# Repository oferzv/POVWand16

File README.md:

# POVWand16

POVWand16 is a 16 LED persistence-of-vision wand. When the wand is moved
through the air, the firmware flashes a vertical column of LEDs fast enough
that the viewer sees complete text or simple bitmap graphics suspended in the
motion path.

The repository contains both sides of the project:

- Arduino firmware for driving the LED column and selecting messages or
  graphics.
- Autodesk Eagle schematic and board layout files for the custom PCB.
- Manufacturing outputs, including a BOM spreadsheet and Gerber archive.

## Project Overview

The design is based around an Arduino Nano-compatible controller connected to
16 individual LEDs. Each LED has its own 100 ohm series resistor. The firmware
writes directly to the AVR port registers for speed, allowing all 16 LEDs to be
updated as a two-byte column pattern.

A trigger input on Arduino analog pin A4 is used to step through the available
display content. The current firmware alternates between text messages and
graphics. Text can be rendered with either the English font table or the Hebrew
font table stored in program memory.

The hardware is intended to be a self-contained handheld wand. The PCB includes
the Arduino Nano footprint, the LED column, a 9 V battery holder, a power slide
switch, a tactile switch, and several header connectors.

## Repository Layout

```text
.
+-- Firmware
|   +-- README.md
|   +-- POVWand16_SW_heb
|       +-- POVWand16.ino
|       +-- font.h
|       +-- python
|           +-- pandaTestFormat.py
+-- Hardware
|   +-- V1_1
|       +-- Eagle
|       |   +-- POVWand16.brd
|       |   +-- POVWand16.sch
|       +-- Manufacturing
|           +-- BOM
|           |   +-- POVWand16_BOM.xlsx
|           +-- Gerber
|               +-- POVWand16_2020-03-09.zip
+-- README.md
```

## Hardware

The hardware design files live under `Hardware/V1_1`.

Main board elements:

- Arduino Nano 3.0-compatible module footprint.
- 16 through-hole 3 mm LEDs labeled `D1` through `D16`.
- 16 through-hole 100 ohm LED current-limiting resistors labeled `R1` through
  `R16`.
- 9 V battery holder footprint.
- Slide power switch.
- 6 mm momentary tactile switch.
- Additional 1x08 and 1x18 headers for board connections and expansion.

The Eagle files are:

- `Hardware/V1_1/Eagle/POVWand16.sch` - schematic.
- `Hardware/V1_1/Eagle/POVWand16.brd` - PCB layout.

Manufacturing files are:

- `Hardware/V1_1/Manufacturing/BOM/POVWand16_BOM.xlsx` - bill of materials.
- `Hardware/V1_1/Manufacturing/Gerber/POVWand16_2020-03-09.zip` - Gerber
  output for PCB fabrication.

## Firmware

The firmware is an Arduino sketch located at:

```text
Firmware/POVWand16_SW_heb/POVWand16.ino
```

Supporting files:

- `font.h` contains the English and Hebrew font tables in `PROGMEM`.
- `python/pandaTestFormat.py` is a small helper script for converting Hebrew
  text into the character order/encoding expected by the sketch.

The sketch uses Arduino pins 2 through 17 as the 16 LED outputs:

```cpp
const byte LEDpins[] = {2, 3, 4, 5, 6, 7, 8, 9, 10, 11, 12, 13, 14, 15, 16, 17};
```

The trigger input is on pin 18, which corresponds to Arduino A4:

```cpp
const byte triggerPin = 18;
```

Display timing is controlled by three constants:

- `charDelay` - spacing between characters.
- `tColDelay` - spacing between text columns.
- `gColDelay` - spacing between graphic columns.

The current firmware defines six text messages and two graphics. A trigger
press advances through the text messages, then advances through the graphics,
then returns to the first text message.

## Display Content

Text messages are defined in `POVWand16.ino` as `PROGMEM` strings:

```cpp
const char textString01 [] PROGMEM = "ARDIUNO - fqjafdya";
const char textString02 [] PROGMEM = "eqfyfxe jyha eay{q";
const char textString03 [] PROGMEM = "BRAVO!";
const char textString04 [] PROGMEM = "Hello";
const char textString05 [] PROGMEM = "WOW!";
const char textString06 [] PROGMEM = "Amazing";
```

Each message is paired with a font type in the `messages_new` table:

- `HEBFONT` selects the Hebrew font table.
- `ENGFONT` selects the English font table.

Graphics are stored as byte arrays in the `graphic` table. Each displayed
column is represented by two bytes, covering the full 16 LED height.

## Building and Uploading

Open `Firmware/POVWand16_SW_heb/POVWand16.ino` in the Arduino IDE or another
Arduino-compatible build environment.

Recommended target:

- Board: Arduino Nano or compatible.
- Processor: the option matching the installed Nano bootloader.
- Upload method: standard USB serial upload through the Nano.

After upload, power the wand and move it through the air. Use the trigger input
to cycle through the stored text and graphic displays.

## Customization Notes

To change displayed text:

1. Edit the `textStringXX` constants in `POVWand16.ino`.
2. Set each message's font type in `messages_new`.
3. Update `NUMBER_OF_ELEMENTS` if the number of messages changes.

To change graphics:

1. Edit the byte arrays in the `graphic` table.
2. Keep each graphic encoded as pairs of bytes per column.
3. Adjust the timing constants if the image appears stretched or compressed
   while waving the wand.

To change LED wiring:

1. Update `LEDpins` if using the slower `digitalWrite` helper path.
2. Update `setPorts()` if changing the direct AVR port mapping used by the
   main display loop.

## Attribution

The firmware is based on the JolliPOV Stick Arduino code from the Instructables
project
[Arduino Based POV Display Stick - JolliPOV Stick](https://www.instructables.com/Arduino-Based-POV-Display-Stick-JolliPOV-Stick/)
by [jollifactory](https://www.instructables.com/member/jollifactory/).

Credit and thanks to the original author for publishing the JolliPOV Stick
project instructions and example firmware.

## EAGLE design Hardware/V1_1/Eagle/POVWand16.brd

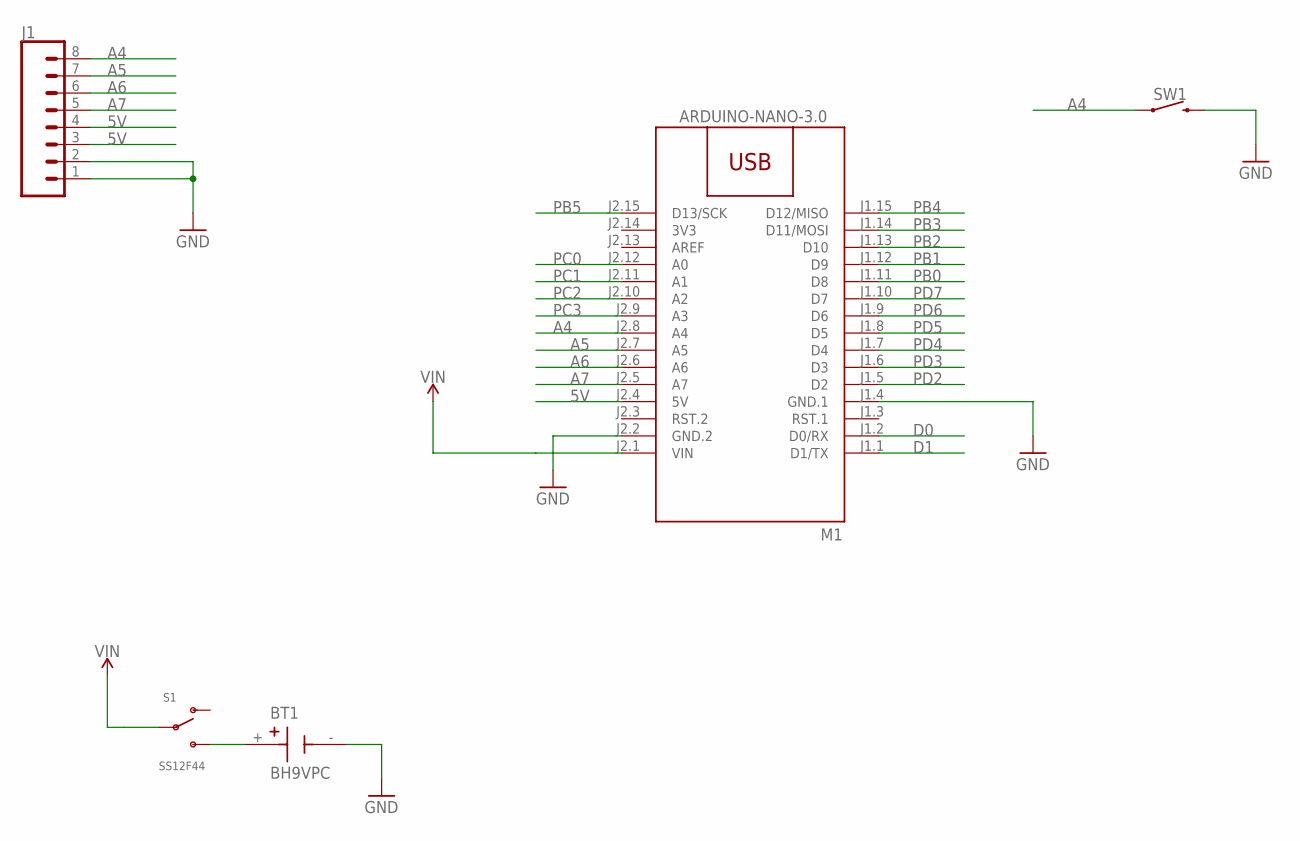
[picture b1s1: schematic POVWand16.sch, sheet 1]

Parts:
BT1: BH9VPC; BAT_BH9VPC
J1: CONN_08"; 1X08
M1: ARDUINO-NANO-3.0
S1: SS12F44; SS12F44G5
SW1: MOMENTARY-SWITCH-SPST_6X6MM; TACT_SW_PTH_6.0MM

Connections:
3V3: M1.J2.14 (3V3)
5V: J1.3, J1.4, M1.J2.4 (5V)
A4: J1.8, M1.J2.8 (A4), SW1.1, SW1.2 (1)
A5: J1.7, M1.J2.7 (A5)
A6: J1.6, M1.J2.6 (A6)
A7: J1.5, M1.J2.5 (A7)
D0: M1.J1.2 (D0/RX); also elsewhere on the board
D1: M1.J1.1 (D1/TX); also elsewhere on the board
GND: BT1.-, J1.1, J1.2, M1.J1.4 (GND.1), M1.J2.2 (GND.2), SW1.3 (2), SW1.4 (2); also elsewhere on the board
unnamed: BT1.+, S1.3 (S)
PB0: M1.J1.11 (D8); also elsewhere on the board
PB1: M1.J1.12 (D9); also elsewhere on the board
PB2: M1.J1.13 (D10); also elsewhere on the board
PB3: M1.J1.14 (D11/MOSI); also elsewhere on the board
PB4: M1.J1.15 (D12/MISO); also elsewhere on the board
PB5: M1.J2.15 (D13/SCK); also elsewhere on the board
PC0: M1.J2.12 (A0); also elsewhere on the board
PC1: M1.J2.11 (A1); also elsewhere on the board
PC2: M1.J2.10 (A2); also elsewhere on the board
PC3: M1.J2.9 (A3); also elsewhere on the board
PD2: M1.J1.5 (D2); also elsewhere on the board
PD3: M1.J1.6 (D3); also elsewhere on the board
PD4: M1.J1.7 (D4); also elsewhere on the board
PD5: M1.J1.8 (D5); also elsewhere on the board
PD6: M1.J1.9 (D6); also elsewhere on the board
PD7: M1.J1.10 (D7); also elsewhere on the board
VIN: M1.J2.1 (VIN), S1.2

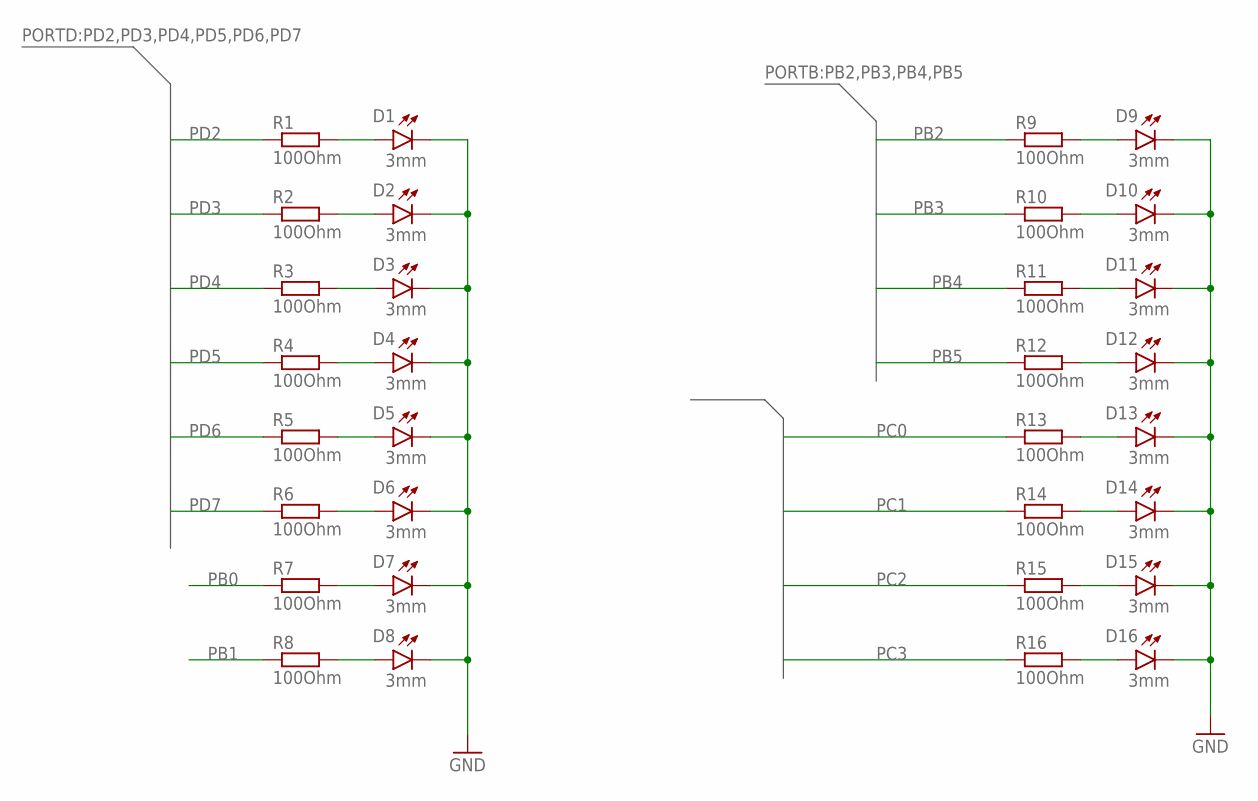
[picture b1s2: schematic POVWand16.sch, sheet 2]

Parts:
D1, D2, D3, D4, D5, D6, D7, D8, D9, D10, D11, D12, D13, D14, D15, D16: 3mm; LED3MM
R1, R2, R3, R4, R5, R6, R7, R8, R9, R10, R11, R12, R13, R14, R15, R16: 100Ohm; 0207/7

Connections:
GND: D1.K (C), D2.K (C), D3.K (C), D4.K (C), D5.K (C), D6.K (C), D7.K (C), D8.K (C), D9.K (C), D10.K (C), D11.K (C), D12.K (C), D13.K (C), D14.K (C), D15.K (C), D16.K (C); also elsewhere on the board
unnamed: D1.A, R1.2
unnamed: D2.A, R2.2
unnamed: D3.A, R3.2
unnamed: D4.A, R4.2
unnamed: D5.A, R5.2
unnamed: D6.A, R6.2
unnamed: D7.A, R7.2
unnamed: D8.A, R8.2
unnamed: D9.A, R9.2
unnamed: D10.A, R10.2
unnamed: D11.A, R11.2
unnamed: D12.A, R12.2
unnamed: D13.A, R13.2
unnamed: D14.A, R14.2
unnamed: D15.A, R15.2
unnamed: D16.A, R16.2
PB0: R7.1; also elsewhere on the board
PB1: R8.1; also elsewhere on the board
PB2: R9.1; also elsewhere on the board
PB3: R10.1; also elsewhere on the board
PB4: R11.1; also elsewhere on the board
PB5: R12.1; also elsewhere on the board
PC0: R13.1; also elsewhere on the board
PC1: R14.1; also elsewhere on the board
PC2: R15.1; also elsewhere on the board
PC3: R16.1; also elsewhere on the board
PD2: R1.1; also elsewhere on the board
PD3: R2.1; also elsewhere on the board
PD4: R3.1; also elsewhere on the board
PD5: R4.1; also elsewhere on the board
PD6: R5.1; also elsewhere on the board
PD7: R6.1; also elsewhere on the board

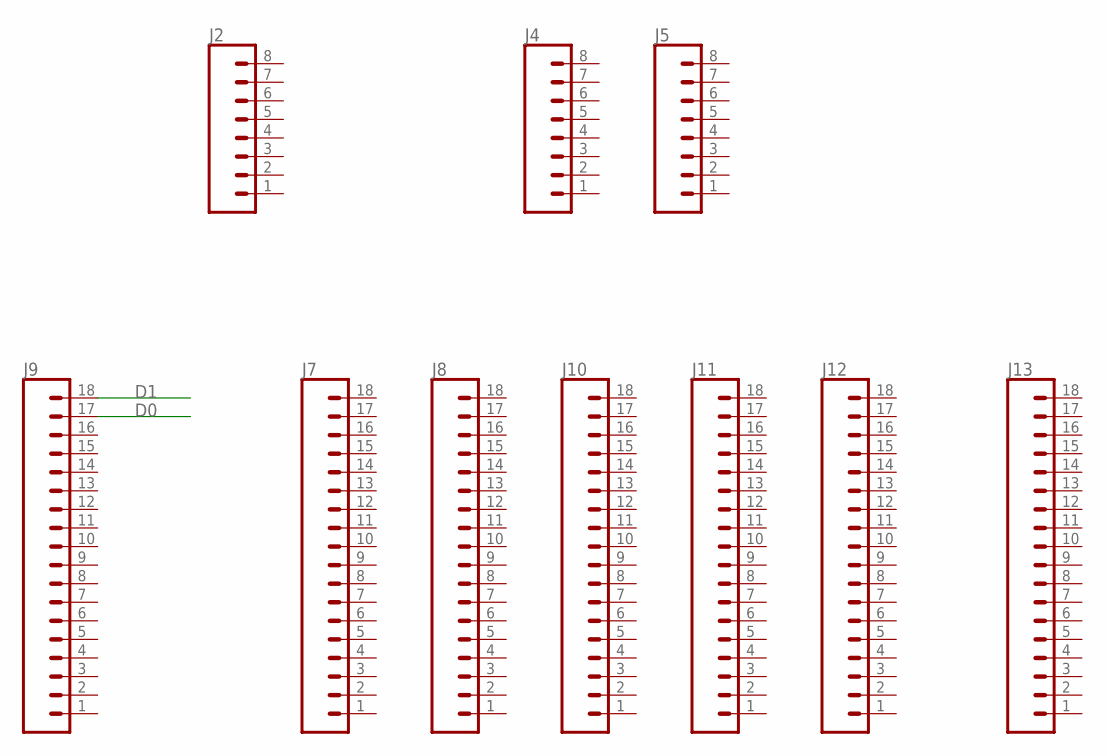
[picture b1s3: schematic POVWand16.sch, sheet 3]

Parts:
J2, J4, J5: CONN_08"; 1X08
J7, J8, J9, J10, J11, J12, J13: CONN_18; 1X18

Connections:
D0: J9.17; also elsewhere on the board
D1: J9.18; also elsewhere on the board

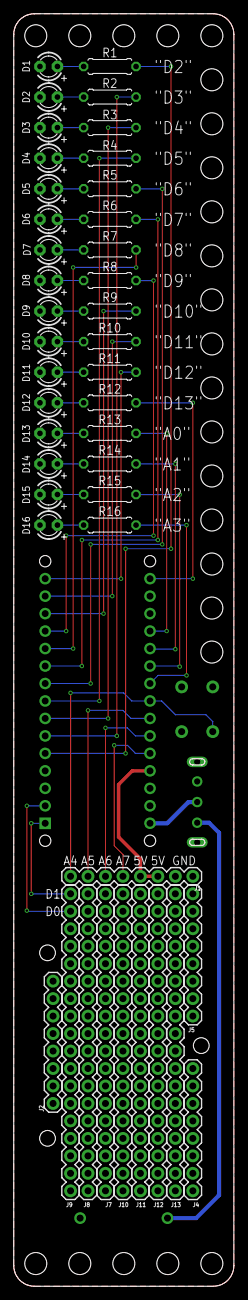
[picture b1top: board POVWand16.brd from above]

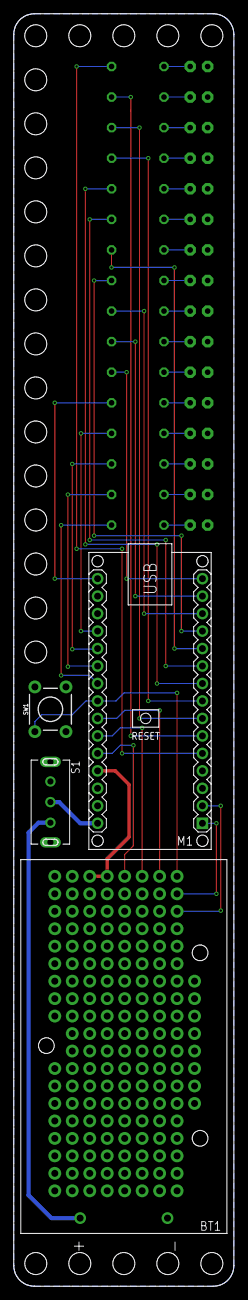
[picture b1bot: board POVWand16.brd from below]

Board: 2 copper layers, 32.0 x 185.0 mm, 47 parts (4 on the bottom side), 42 nets.

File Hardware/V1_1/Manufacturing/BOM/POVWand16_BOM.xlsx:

povTest BOM
# | Qty | Parts | MF | MPN | PRICE | TOTAL | VALUE | FOOTPRINT | DESCRIPTION
1 | 1 | SW1 | C&K | PTS645SM43-2 LFS | 0.04 | 0.04 |  | 6.00mm x 6.00mm | SWITCH TACTILE SPST-NO 0.05A 12V | https://www.taydaelectronics.com/electromechanical/switches-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
2 | 16 | R1, R2, R3, R4, R5, R6, R7, R8, R9, R10, R11, R12, R13, R14, R15, R16 |  |  | 1.2E-2 | 0.192 | 100Ohm | T/H |  | https://www.taydaelectronics.com/resistors/1-4w-metal-film-r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
3 | 16 | D1, D2, D3, D4, D5, D6, D7, D8, D9, D10, D11, D12, D13, D14, D15, D16 |  |  | 0.02 | 0.32 | 3mm | RADIAL 3MM |  | https://www.taydaelectronics.com/leds/round-leds/3mm-leds/le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
4 | 2 |  |  |  | 0.12 | 0.24 |  |  | 15 PIN 2.54MM SINGLE ROW FEMALE PIN HEADER | https://www.taydaelectronics.com/connectors-sockets/pin-head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
5 | 1 | M1 |  |  | 3.69 | 3.69 |  |  | NANO 3.0 CONTROLLER COMPATIBLE WITH ARDUINO NANO CH340 USB DRIVER | https://www.taydaelectronics.com/nano-3-0-controller-compati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
6 | 1 | BT1 | MPD _Memory | BH9VPC | 0.47 | 0.47 |  |  | Battery Holder _Open_ 9V 1 Cell PC Pin | https://www.taydaelectronics.com/9v-battery-holder-6.html
7 | 1 | S1 |  | SS12F44G5 | 0.05 | 0.05 |  |  | SLIDE SWITCH 1P2T THROUGH HOLE 0.5A 50VDC | https://www.taydaelectronics.com/electromechanical/switches-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
 |  |  |  |  |  | 5.0019999999999998

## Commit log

2026-06-06 Ignore Excel temporary files
2026-06-06 Add Hebrew string processing script and update README
    - Introduced a new Python script `pandaTestFormat.py` for processing Hebrew strings.
    - The script accepts a Hebrew string as input, decodes it, and outputs a modified version.
    - Added a README file to provide context and credit for the firmware based on the JolliPOV Stick project.
    - Included a new BOM Excel file for manufacturing reference.
2026-06-07 Update project README

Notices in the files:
parts and their libraries:
SparkFun-Connectors: Licensing: Creative Commons ShareAlike 4.0 International - https://creativecommons.org/licenses/by-sa/4.0
